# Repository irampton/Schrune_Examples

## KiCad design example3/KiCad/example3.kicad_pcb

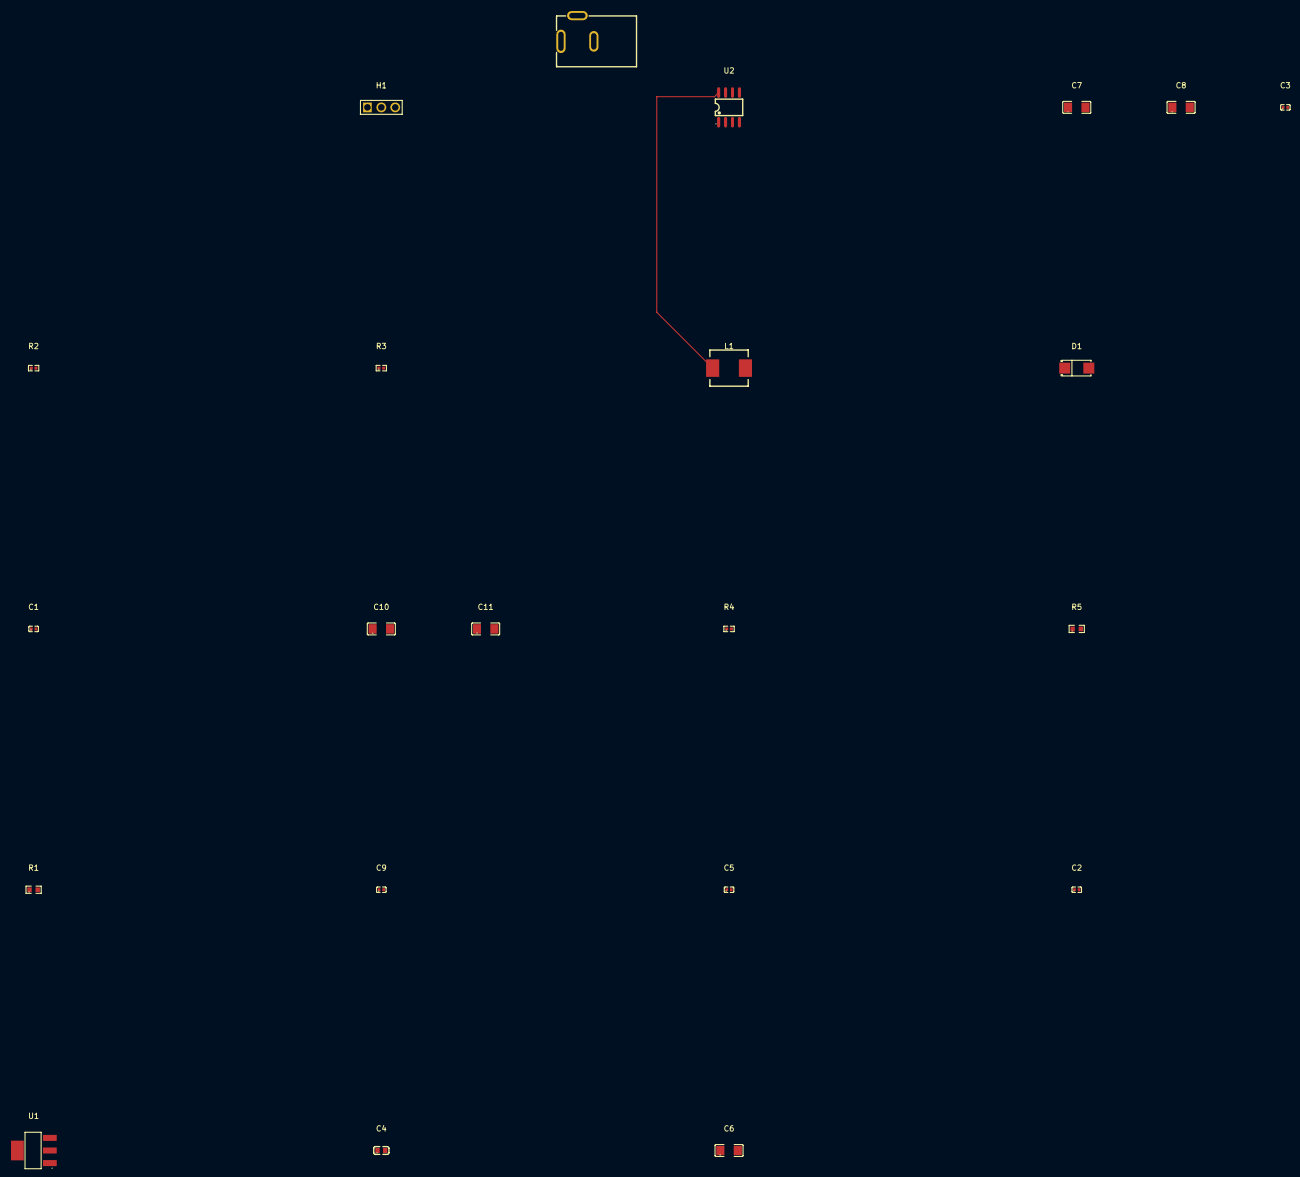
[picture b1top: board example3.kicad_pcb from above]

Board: 2 copper layers, 22 parts (0 on the bottom side), 11 nets.

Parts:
C1: 100nF +/- 10%; CL05B104KO5NNNC
C2, C3: 10nF +/- 10%; P_0402B103K500NT
C4: 10uF +/- 20%; CL10A106MQ8NNNC
C5: 1nF +/- 10%; P_0402B102K500NT
C6: 22uF +/- 20%; CL31A226MOHNNNE
C7, C8: 4.7uF +/- 20%; P_1206B475K500NT
C9: 47pF +/- 5%; P_0402CG470J500NT
C10, C11: 47uF +/- 20%; CL31A476MQHNNNE
D1: Diode; SS34
DC1: PJ-002BH; PJ_002BH
H1: 2.54-1*3P针; P_2_54_1_3P
L1: Inductor; SL0630_6R8M
R1: 30kohm +/- 1%; P_0603WAJ0303T5E
R2: 330kohm +/- 1%; RTT02334JTH
R3: 68kohm +/- 1%; RTT02683JTH
R4: 10000kOhm; P_0402WGF1005TCE
R5: 1904.7619047619046; RCT034R7JLF
U1: AMS1117-3.3; AMS1117_3_3
U2: TPS54331DR

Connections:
GND: C2.2, C3.2, C4.2, C6.2, C7.2, C8.2, C9.2, C10.2, C11.2, D1.1, DC1.2, DC1.3, H1.1, R1.2, R3.2, R5.2, U1.1, U2.7
VIN_h: C3.1, C7.1, C8.1, DC1.1, R2.1, U2.2
boot_cap_1: C1.2, D1.2, L1.1, U2.8
comp_c2_1: C5.2, R1.1
en_r1_1: R2.2, R3.1, U2.3
fb_r1_1: R4.2, R5.1, U2.5
power_3v3_h: C6.1, H1.3, U1.2
power_5v_h: C4.1, C10.1, C11.1, H1.2, L1.2, R4.1, U1.3
regulator_BOOT: C1.1, U2.1
regulator_COMP: C5.1, C9.1, U2.6
regulator_SS: C2.1, U2.4

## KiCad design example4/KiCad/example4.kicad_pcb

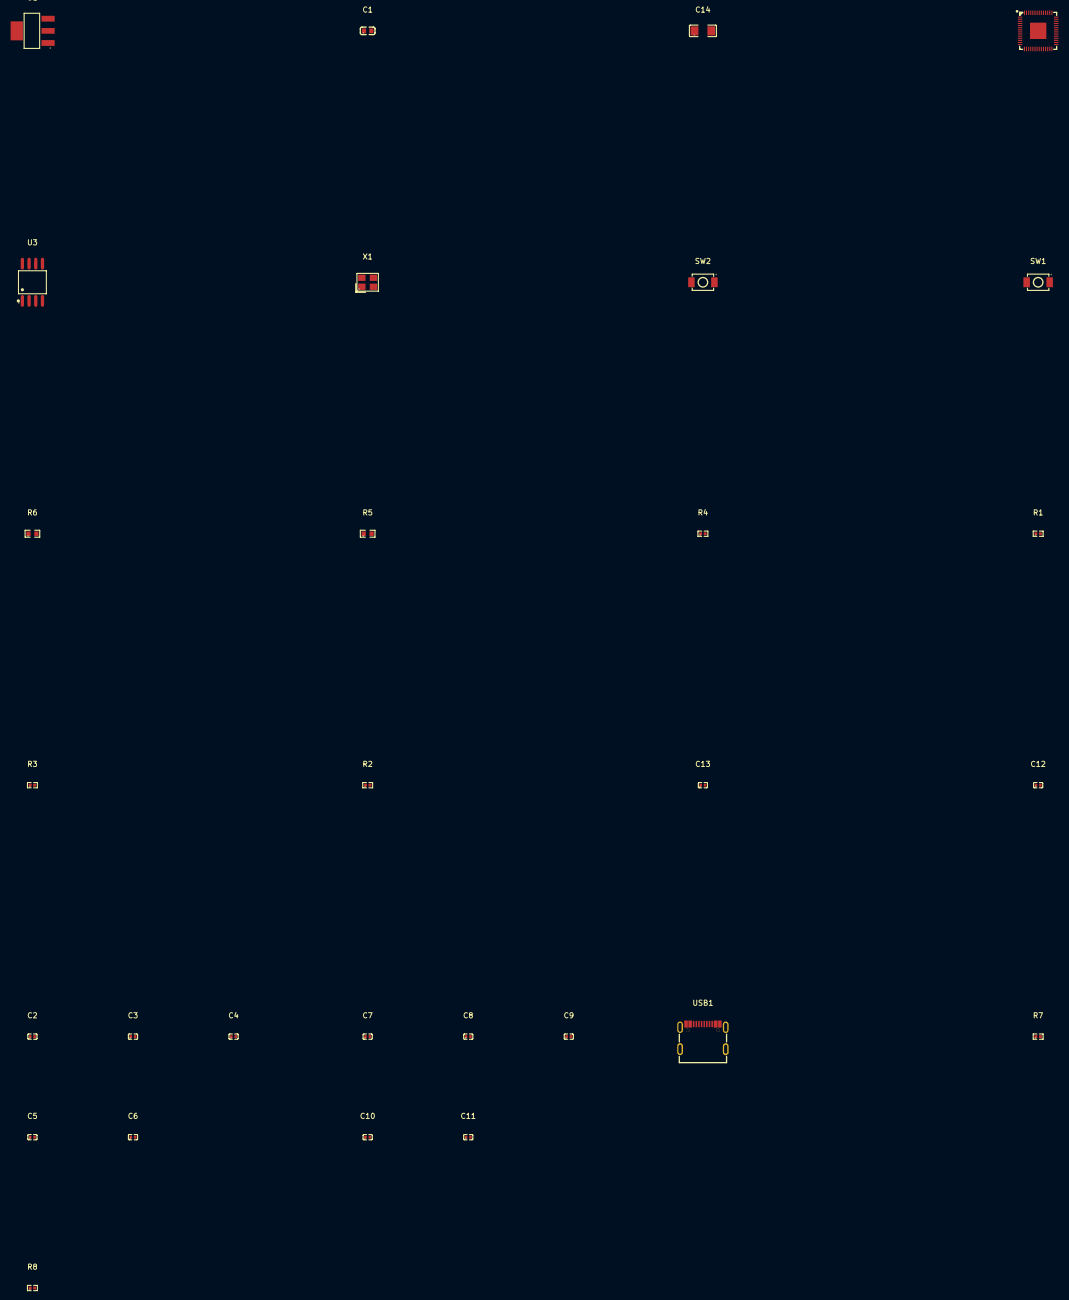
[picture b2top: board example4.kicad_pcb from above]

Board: 2 copper layers, 29 parts (0 on the bottom side), 22 nets, no tracks yet.

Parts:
C1: 10uF +/- 20%; C0603
C2, C3, C4, C5, C6, C7, C8, C9, C10, C11: 1uF +/- 20%; C0402
C12, C13: 20pF +/- 20%; C0402
C14: 22uF +/- 20%; C1206
R1, R2, R3, R4: 10kohms +/- 5%; R0402
R5, R6: 22Ohm +/- 5%; R0603
R7, R8: 5.1kohms +/- 5%; R0402
SW1, SW2: TS-1088-AR02016; SW-SMD_L3.9-W3.0-P4.45
U1: AMS1117-3.3; SOT-223-3_L6.5-W3.4-P2.30-LS7.0-BR
U2: RP2040; LQFN-56_L7.0-W7.0-P0.4-EP
U3: W25Q128JVSIQ; SOIC-8_L5.3-W5.3-P1.27-LS8.0-BL
USB1: UC09-0B16F00P11; USB-C_UC09-0B16F00P11
X1: X322512MSB4SI; CRYSTAL-SMD_4P-L3.2-W2.5-BL

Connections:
boot_btn_2: R1.1, SW1.2
crystal_OSC2: C12.1, R2.1, X1.3
crystal_res_1: R2.2, U2.21
flash_CLK: U2.52, U3.6
flash_CS: R1.2, R3.2, U2.56, U3.1
flash_DI: U2.53, U3.5
flash_DO: U2.55, U3.2
flash_IO2: U2.54, U3.3
flash_IO3: U2.51, U3.7
package_XIN: C13.1, U2.20, X1.1
power_3v3_h: C2.2, C3.2, C4.2, C5.2, C6.2, C14.1, R3.1, R4.1, U1.2, U3.8
power_3v3_l: C1.2, C2.1, C3.1, C4.1, C5.1, C6.1, C7.1, C8.1, C9.1, C10.1, C11.1, C12.2, C13.2, C14.2, SW1.1, SW2.1, U1.1, U3.4, X1.2, X1.4
power_5v_h: C1.1, U1.3, USB1.A4B9, USB1.B4A9
power_5v_l: R7.2, R8.2, USB1.A1B12, USB1.B1A12
reset_btn_pullup_1: R4.2, SW2.2, U2.26
rp2040_power_1v8_h: C7.2, C8.2, C9.2, C10.2, C11.2
rp2040_usb_n: R5.1, USB1.A7, USB1.B7
rp2040_usb_p: R6.1, USB1.A6, USB1.B6
usb_CC1: R7.1, USB1.A5
usb_CC2: R8.1, USB1.B5
usb_series_resistors_0_1: R6.2, U2.47
usb_series_resistors_1_1: R5.2, U2.46

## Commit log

2026-06-24 First pass of examples
